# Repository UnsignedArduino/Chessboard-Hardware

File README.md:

[Chessboard-Hardware](https://github.com/UnsignedArduino/Chessboard-Hardware) |
[Chessboard-Design](https://github.com/UnsignedArduino/Chessboard-Design) |
[Chessboard-Nano](https://github.com/UnsignedArduino/Chessboard-Nano) |
[Chessboard-Pi](https://github.com/UnsignedArduino/Chessboard-Pi)

# Chessboard-Hardware

Hardware for a magnetic-piece-tracking digital chessboard! WIP

This repository contains the KiCad PCB project for the majority of the Chessboard's wiring.

## Notes

### Models

All models were modified in Fusion 360. 

* Arduino Nano was modified from [Joel Skerman's model](https://www.thingiverse.com/thing:3863918) and colors are inspired by
  [Raafat Mohamed's model](https://grabcad.com/library/arduino-nano-26).
* SS49E was modified from the [SnapMagic library](https://www.snapeda.com/parts/SS49E/Honeywell/view-part/?ref=digikey).

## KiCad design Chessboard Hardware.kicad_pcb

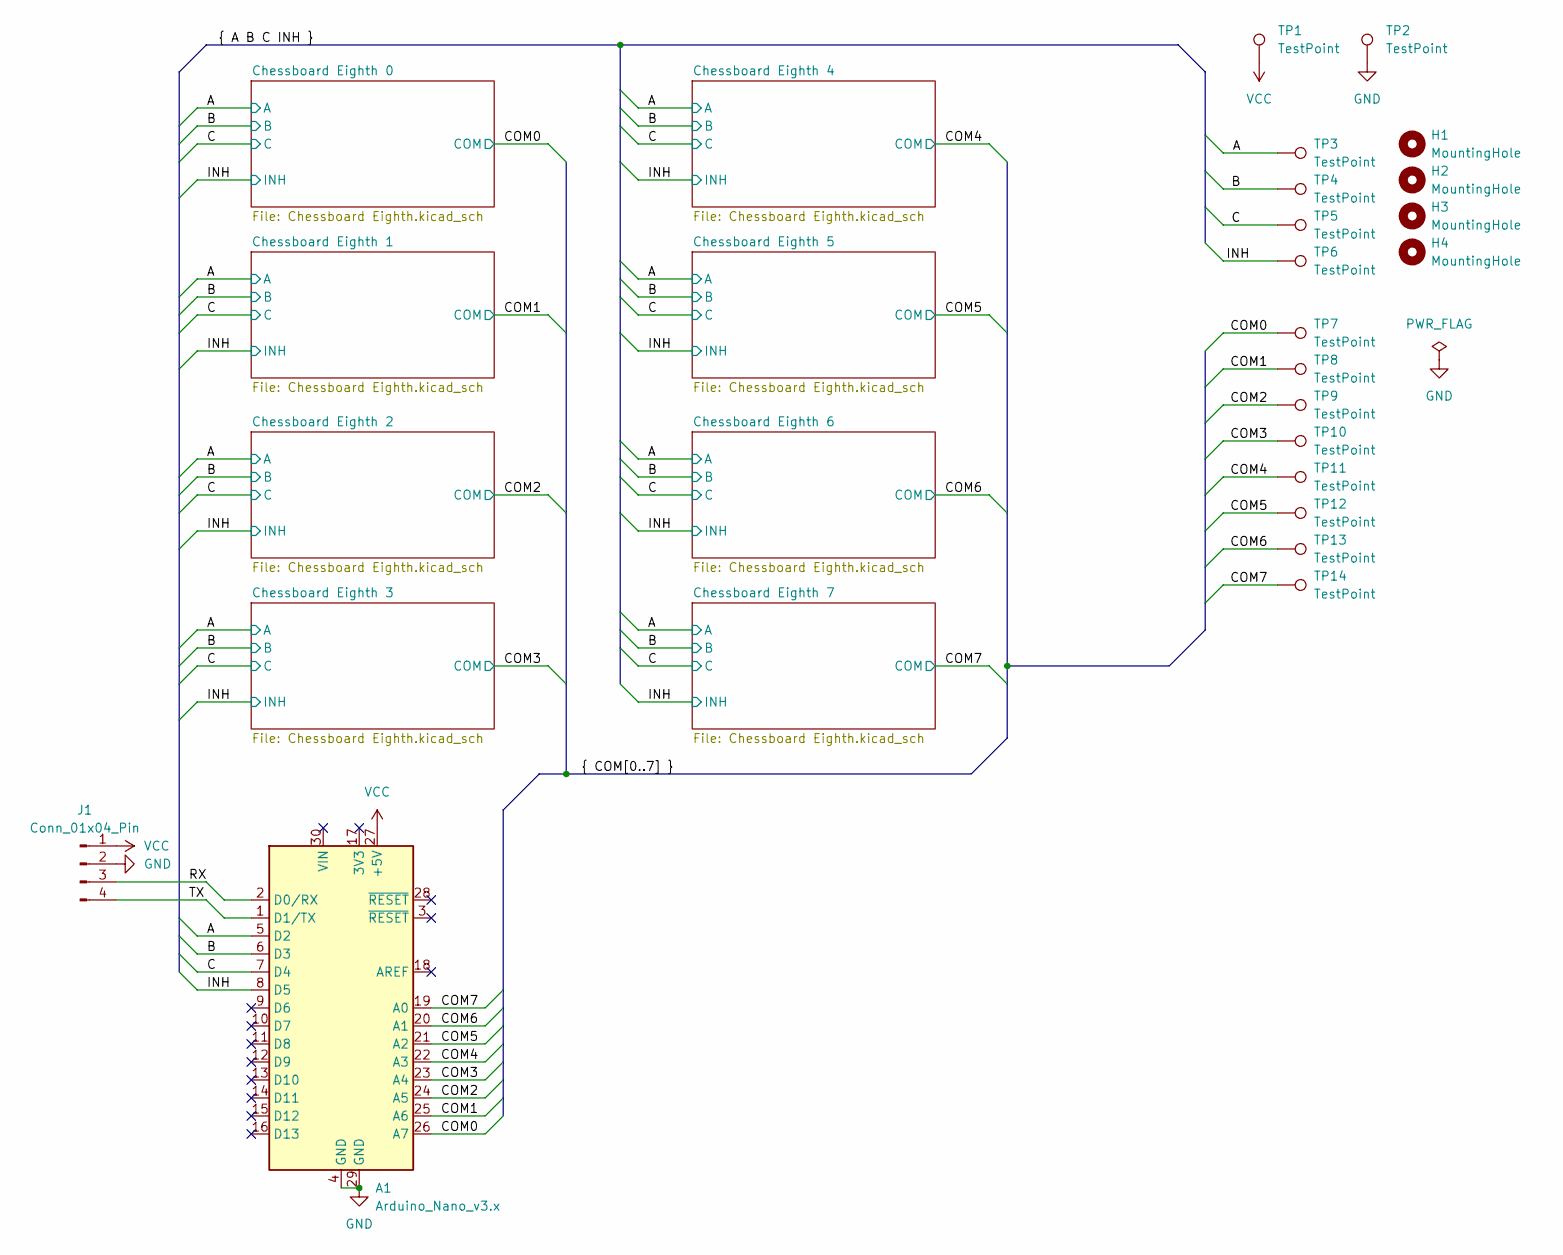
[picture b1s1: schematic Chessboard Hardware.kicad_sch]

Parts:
A1: Arduino_Nano_v3.x; Arduino_Nano
H1, H2, H3, H4: MountingHole; MountingHole_2.7mm_M2.5
J1: Conn_01x04_Pin; JST_XH_B4B-XH-A_1x04_P2.50mm_Vertical
TP1, TP2, TP3, TP4, TP5, TP6, TP7, TP8, TP9, TP10, TP11, TP12, TP13, TP14: TestPoint; PinHeader_1x01_P2.54mm_Vertical

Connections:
/A: A1.5 (D2), TP3.1; also elsewhere on the board
/B: A1.6 (D3), TP4.1; also elsewhere on the board
/C: A1.7 (D4), TP5.1; also elsewhere on the board
/COM0: A1.26 (A7), TP7.1; also elsewhere on the board
/COM1: A1.25 (A6), TP8.1; also elsewhere on the board
/COM2: A1.24 (A5), TP9.1; also elsewhere on the board
/COM3: A1.23 (A4), TP10.1; also elsewhere on the board
/COM4: A1.22 (A3), TP11.1; also elsewhere on the board
/COM5: A1.21 (A2), TP12.1; also elsewhere on the board
/COM6: A1.20 (A1), TP13.1; also elsewhere on the board
/COM7: A1.19 (A0), TP14.1; also elsewhere on the board
/INH: A1.8 (D5), TP6.1; also elsewhere on the board
/RX: A1.2 (D0/RX), J1.3
/TX: A1.1 (D1/TX), J1.4
GND: A1.4 (GND), A1.29 (GND), J1.2, TP2.1; also elsewhere on the board
VCC: A1.27 (+5V), J1.1, TP1.1; also elsewhere on the board

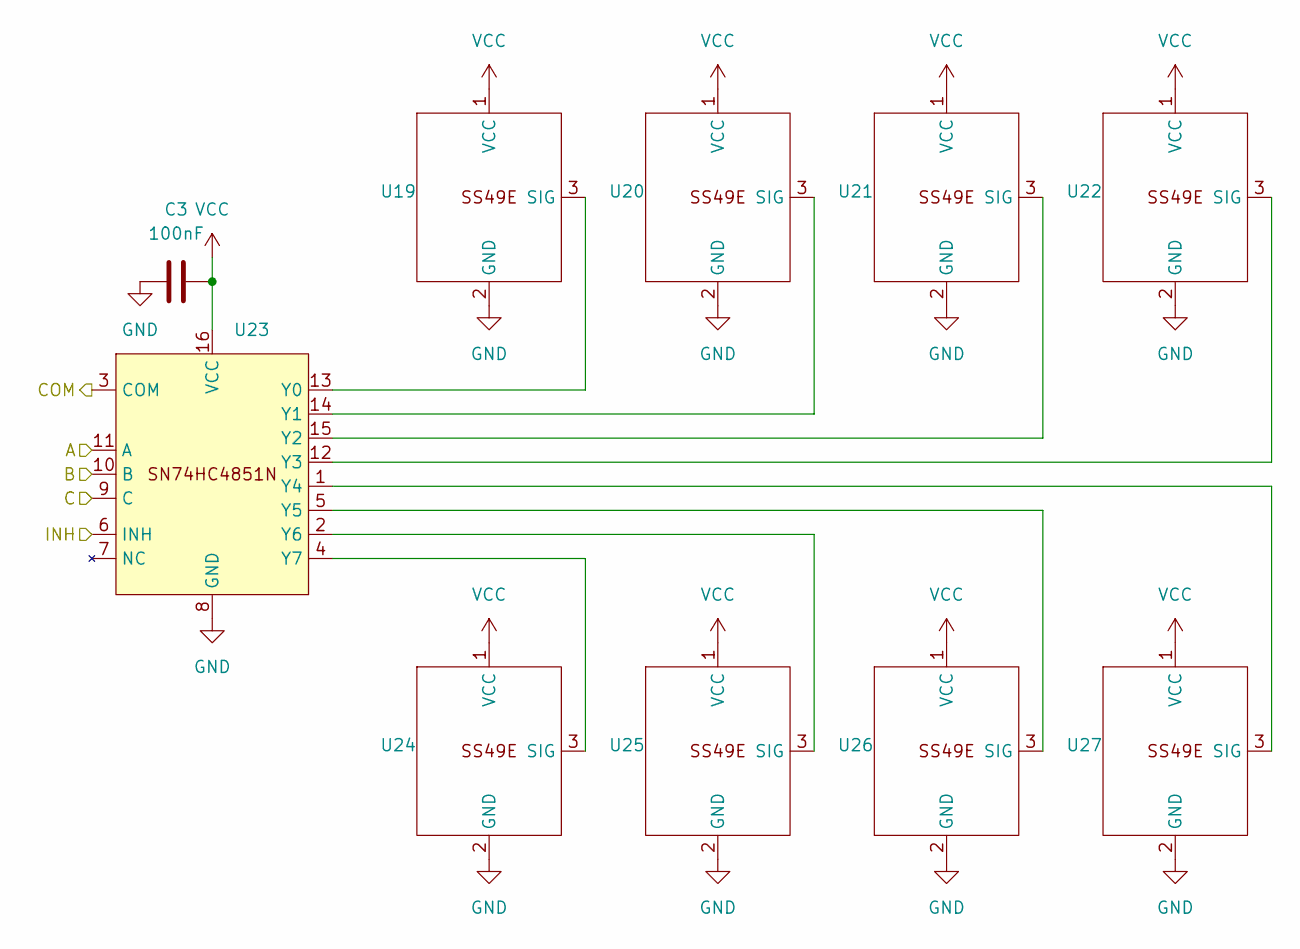
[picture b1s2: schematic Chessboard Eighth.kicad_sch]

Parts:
C3: 100nF; C_Disc_D5.0mm_W2.5mm_P2.50mm
U19, U20, U21, U22, U24, U25, U26, U27: SS49E
U23: DIP-16_W7.62mm

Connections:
/A: U23.11 (A); also elsewhere on the board
/B: U23.10 (B); also elsewhere on the board
/C: U23.9 (C); also elsewhere on the board
/COM2: U23.3 (COM); also elsewhere on the board
/INH: U23.6 (INH); also elsewhere on the board
GND: C3.1, U19.2 (GND), U20.2 (GND), U21.2 (GND), U22.2 (GND), U23.8 (GND), U24.2 (GND), U25.2 (GND), U26.2 (GND), U27.2 (GND); also elsewhere on the board
unnamed: U19.3 (SIG), U23.13 (Y0)
unnamed: U20.3 (SIG), U23.14 (Y1)
unnamed: U21.3 (SIG), U23.15 (Y2)
unnamed: U22.3 (SIG), U23.12 (Y3)
unnamed: U23.1 (Y4), U27.3 (SIG)
unnamed: U23.5 (Y5), U26.3 (SIG)
unnamed: U23.2 (Y6), U25.3 (SIG)
unnamed: U23.4 (Y7), U24.3 (SIG)
VCC: C3.2, U19.1 (VCC), U20.1 (VCC), U21.1 (VCC), U22.1 (VCC), U23.16 (VCC), U24.1 (VCC), U25.1 (VCC), U26.1 (VCC), U27.1 (VCC); also elsewhere on the board

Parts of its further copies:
C1, C2, C4, C5, C6, C7, C8: 100nF; C_Disc_D5.0mm_W2.5mm_P2.50mm
U1, U2, U3, U4, U6, U7, U8, U9, U10, U11, U12, U13, U15, U16, U17, U18, U28, U29, U30, U31, U33, U34, U35, U36, U37, U38, U39, U40, U42, U43, U44, U45, U46, U47, U48, U49, U51, U52, U53, U54, U55, U56, U57, U58, U60, U61, U62, U63, U64, U65, U66, U67, U69, U70, U71, U72: SS49E
U5, U14, U32, U41, U50, U59, U68: DIP-16_W7.62mm

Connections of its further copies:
/A: U5.11 (A), U14.11 (A), U32.11 (A), U41.11 (A), U50.11 (A), U59.11 (A), U68.11 (A); also elsewhere on the board
/B: U5.10 (B), U14.10 (B), U32.10 (B), U41.10 (B), U50.10 (B), U59.10 (B), U68.10 (B); also elsewhere on the board
/C: U5.9 (C), U14.9 (C), U32.9 (C), U41.9 (C), U50.9 (C), U59.9 (C), U68.9 (C); also elsewhere on the board
/COM0: U5.3 (COM); also elsewhere on the board
/COM1: U14.3 (COM); also elsewhere on the board
/COM3: U32.3 (COM); also elsewhere on the board
/COM4: U41.3 (COM); also elsewhere on the board
/COM5: U50.3 (COM); also elsewhere on the board
/COM6: U59.3 (COM); also elsewhere on the board
/COM7: U68.3 (COM); also elsewhere on the board
/INH: U5.6 (INH), U14.6 (INH), U32.6 (INH), U41.6 (INH), U50.6 (INH), U59.6 (INH), U68.6 (INH); also elsewhere on the board
GND: C1.1, C2.1, C4.1, C5.1, C6.1, C7.1, C8.1, U1.2 (GND), U2.2 (GND), U3.2 (GND), U4.2 (GND), U5.8 (GND), U6.2 (GND), U7.2 (GND), U8.2 (GND), U9.2 (GND), U10.2 (GND), U11.2 (GND), U12.2 (GND), U13.2 (GND), U14.8 (GND), U15.2 (GND), U16.2 (GND), U17.2 (GND), U18.2 (GND), U28.2 (GND), U29.2 (GND), U30.2 (GND), U31.2 (GND), U32.8 (GND), U33.2 (GND), U34.2 (GND), U35.2 (GND), U36.2 (GND), U37.2 (GND), U38.2 (GND), U39.2 (GND), U40.2 (GND), U41.8 (GND), U42.2 (GND), U43.2 (GND), U44.2 (GND), U45.2 (GND), U46.2 (GND), U47.2 (GND), U48.2 (GND), U49.2 (GND), U50.8 (GND), U51.2 (GND), U52.2 (GND), U53.2 (GND), U54.2 (GND), U55.2 (GND), U56.2 (GND), U57.2 (GND), U58.2 (GND), U59.8 (GND), U60.2 (GND), U61.2 (GND), U62.2 (GND), U63.2 (GND), U64.2 (GND), U65.2 (GND), U66.2 (GND), U67.2 (GND), U68.8 (GND), U69.2 (GND), U70.2 (GND), U71.2 (GND), U72.2 (GND); also elsewhere on the board
unnamed: U1.3 (SIG), U5.13 (Y0)
unnamed: U2.3 (SIG), U5.14 (Y1)
unnamed: U3.3 (SIG), U5.15 (Y2)
unnamed: U4.3 (SIG), U5.12 (Y3)
unnamed: U5.1 (Y4), U9.3 (SIG)
unnamed: U5.5 (Y5), U8.3 (SIG)
unnamed: U5.2 (Y6), U7.3 (SIG)
unnamed: U5.4 (Y7), U6.3 (SIG)
unnamed: U10.3 (SIG), U14.13 (Y0)
unnamed: U11.3 (SIG), U14.14 (Y1)
unnamed: U12.3 (SIG), U14.15 (Y2)
unnamed: U13.3 (SIG), U14.12 (Y3)
unnamed: U14.1 (Y4), U18.3 (SIG)
unnamed: U14.5 (Y5), U17.3 (SIG)
unnamed: U14.2 (Y6), U16.3 (SIG)
unnamed: U14.4 (Y7), U15.3 (SIG)
unnamed: U28.3 (SIG), U32.13 (Y0)
unnamed: U29.3 (SIG), U32.14 (Y1)
unnamed: U30.3 (SIG), U32.15 (Y2)
unnamed: U31.3 (SIG), U32.12 (Y3)
unnamed: U32.1 (Y4), U36.3 (SIG)
unnamed: U32.5 (Y5), U35.3 (SIG)
unnamed: U32.2 (Y6), U34.3 (SIG)
unnamed: U32.4 (Y7), U33.3 (SIG)
unnamed: U37.3 (SIG), U41.13 (Y0)
unnamed: U38.3 (SIG), U41.14 (Y1)
unnamed: U39.3 (SIG), U41.15 (Y2)
unnamed: U40.3 (SIG), U41.12 (Y3)
unnamed: U41.1 (Y4), U45.3 (SIG)
unnamed: U41.5 (Y5), U44.3 (SIG)
unnamed: U41.2 (Y6), U43.3 (SIG)
unnamed: U41.4 (Y7), U42.3 (SIG)
unnamed: U46.3 (SIG), U50.13 (Y0)
unnamed: U47.3 (SIG), U50.14 (Y1)
unnamed: U48.3 (SIG), U50.15 (Y2)
unnamed: U49.3 (SIG), U50.12 (Y3)
unnamed: U50.1 (Y4), U54.3 (SIG)
unnamed: U50.5 (Y5), U53.3 (SIG)
unnamed: U50.2 (Y6), U52.3 (SIG)
unnamed: U50.4 (Y7), U51.3 (SIG)
unnamed: U55.3 (SIG), U59.13 (Y0)
unnamed: U56.3 (SIG), U59.14 (Y1)
unnamed: U57.3 (SIG), U59.15 (Y2)
unnamed: U58.3 (SIG), U59.12 (Y3)
unnamed: U59.1 (Y4), U63.3 (SIG)
unnamed: U59.5 (Y5), U62.3 (SIG)
unnamed: U59.2 (Y6), U61.3 (SIG)
unnamed: U59.4 (Y7), U60.3 (SIG)
unnamed: U64.3 (SIG), U68.13 (Y0)
unnamed: U65.3 (SIG), U68.14 (Y1)
unnamed: U66.3 (SIG), U68.15 (Y2)
unnamed: U67.3 (SIG), U68.12 (Y3)
unnamed: U68.1 (Y4), U72.3 (SIG)
unnamed: U68.5 (Y5), U71.3 (SIG)
unnamed: U68.2 (Y6), U70.3 (SIG)
unnamed: U68.4 (Y7), U69.3 (SIG)
VCC: C1.2, C2.2, C4.2, C5.2, C6.2, C7.2, C8.2, U1.1 (VCC), U2.1 (VCC), U3.1 (VCC), U4.1 (VCC), U5.16 (VCC), U6.1 (VCC), U7.1 (VCC), U8.1 (VCC), U9.1 (VCC), U10.1 (VCC), U11.1 (VCC), U12.1 (VCC), U13.1 (VCC), U14.16 (VCC), U15.1 (VCC), U16.1 (VCC), U17.1 (VCC), U18.1 (VCC), U28.1 (VCC), U29.1 (VCC), U30.1 (VCC), U31.1 (VCC), U32.16 (VCC), U33.1 (VCC), U34.1 (VCC), U35.1 (VCC), U36.1 (VCC), U37.1 (VCC), U38.1 (VCC), U39.1 (VCC), U40.1 (VCC), U41.16 (VCC), U42.1 (VCC), U43.1 (VCC), U44.1 (VCC), U45.1 (VCC), U46.1 (VCC), U47.1 (VCC), U48.1 (VCC), U49.1 (VCC), U50.16 (VCC), U51.1 (VCC), U52.1 (VCC), U53.1 (VCC), U54.1 (VCC), U55.1 (VCC), U56.1 (VCC), U57.1 (VCC), U58.1 (VCC), U59.16 (VCC), U60.1 (VCC), U61.1 (VCC), U62.1 (VCC), U63.1 (VCC), U64.1 (VCC), U65.1 (VCC), U66.1 (VCC), U67.1 (VCC), U68.16 (VCC), U69.1 (VCC), U70.1 (VCC), U71.1 (VCC), U72.1 (VCC); also elsewhere on the board

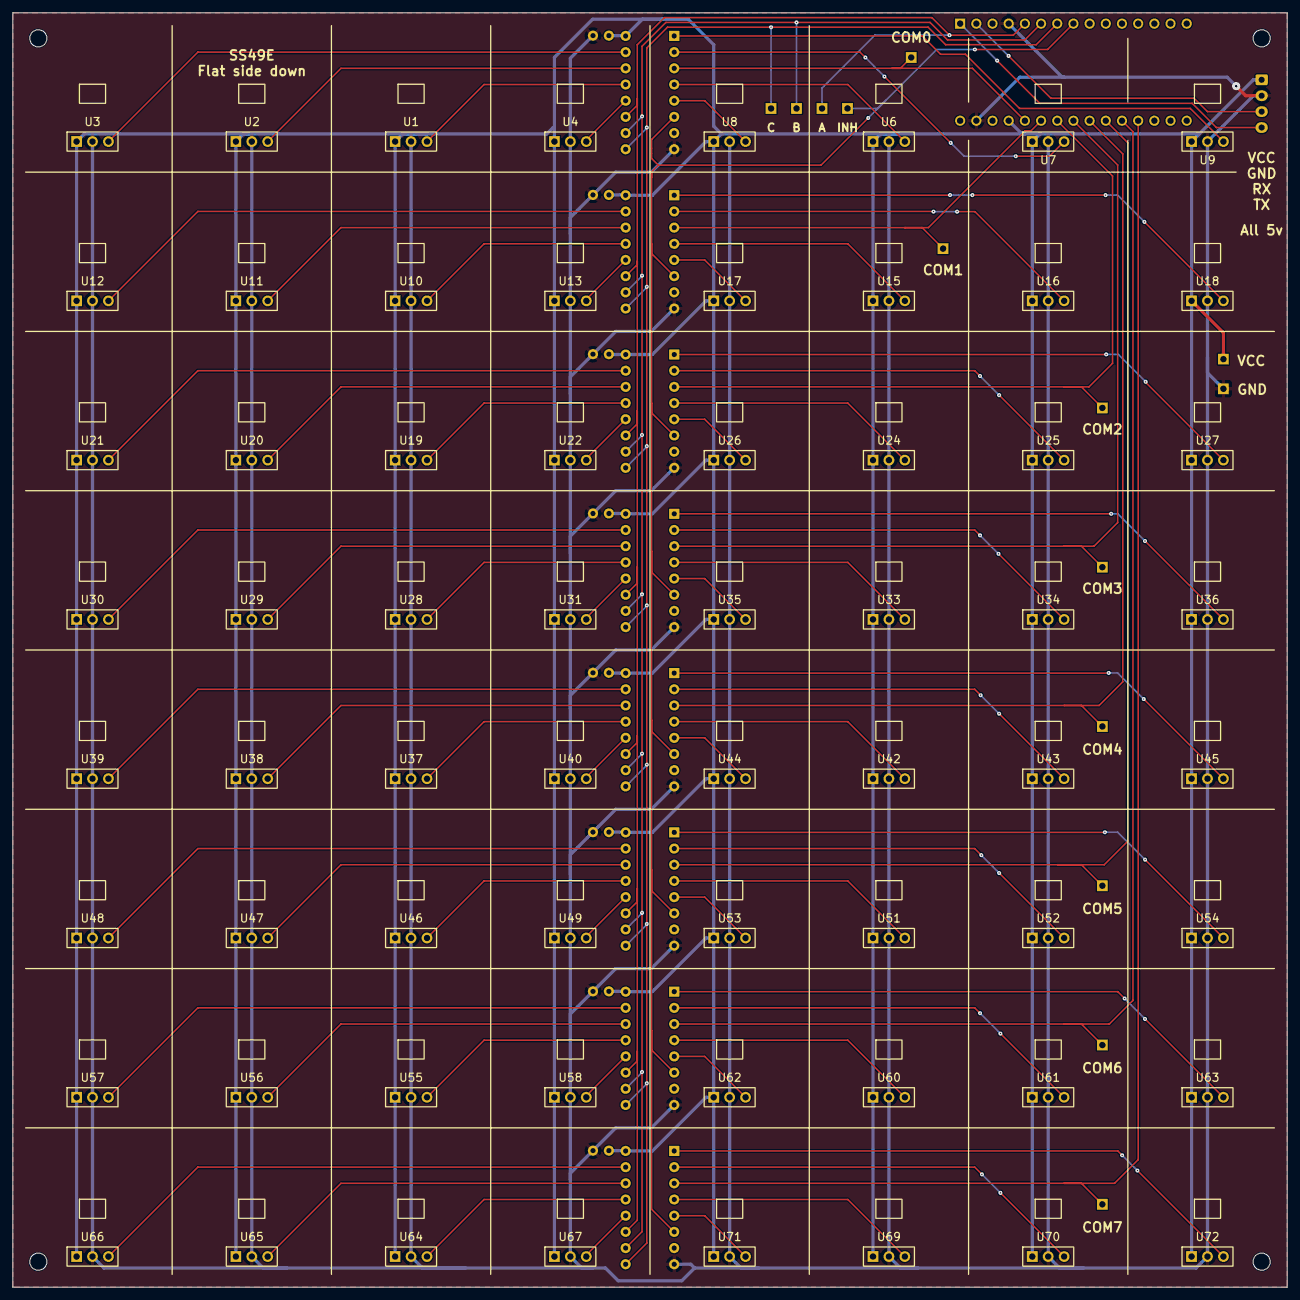
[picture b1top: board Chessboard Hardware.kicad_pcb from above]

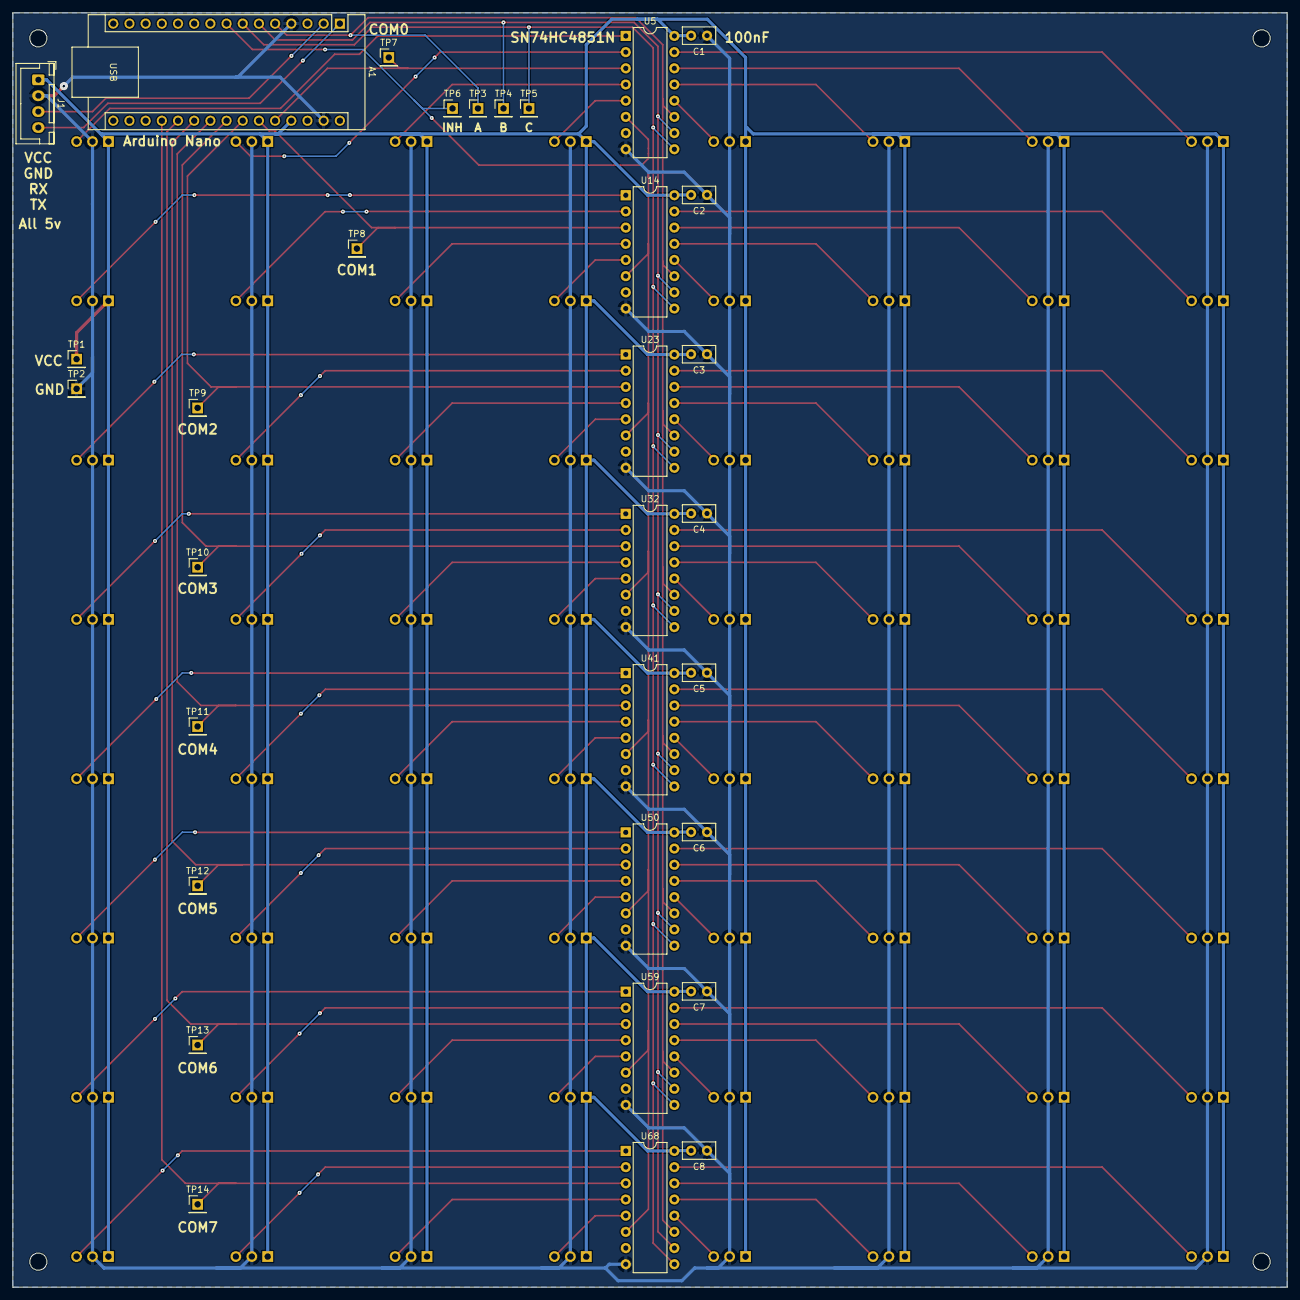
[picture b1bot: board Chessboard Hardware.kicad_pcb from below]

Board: 2 copper layers, 200.0 x 200.0 mm, 100 parts (32 on the bottom side), 80 nets.

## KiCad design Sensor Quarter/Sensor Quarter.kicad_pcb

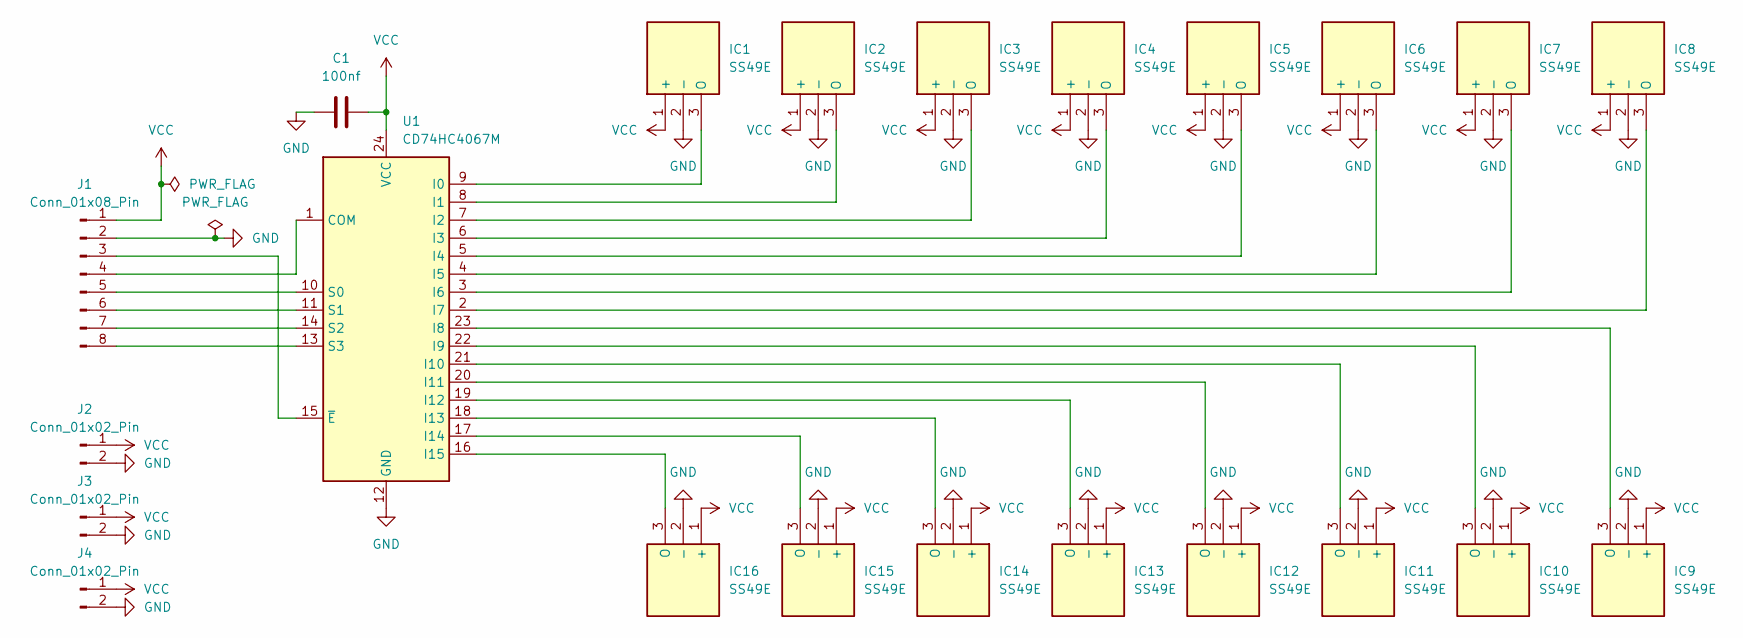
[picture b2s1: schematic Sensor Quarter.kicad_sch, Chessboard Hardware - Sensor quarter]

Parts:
C1: 100nf; C_Disc_D5.0mm_W2.5mm_P2.50mm
IC1, IC2, IC3, IC4, IC5, IC6, IC7, IC8, IC9, IC10, IC11, IC12, IC13, IC14, IC15, IC16: SS49E; TO130P160X410X300-3P; Manufacturer_Part_Number SS49E; Mouser Part Number 785-SS49E
J1: Conn_01x08_Pin; PinHeader_1x08_P2.54mm_Vertical
J2, J3, J4: Conn_01x02_Pin; PinHeader_1x02_P2.54mm_Vertical
U1: CD74HC4067M; SOIC-24W_7.5x15.4mm_P1.27mm

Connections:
GND: C1.1, IC1.2 (-), IC2.2 (-), IC3.2 (-), IC4.2 (-), IC5.2 (-), IC6.2 (-), IC7.2 (-), IC8.2 (-), IC9.2 (-), IC10.2 (-), IC11.2 (-), IC12.2 (-), IC13.2 (-), IC14.2 (-), IC15.2 (-), IC16.2 (-), J1.2, J2.2, J3.2, J4.2, U1.12 (GND)
unnamed: IC1.3 (O), U1.9 (I0)
unnamed: IC2.3 (O), U1.8 (I1)
unnamed: IC3.3 (O), U1.7 (I2)
unnamed: IC4.3 (O), U1.6 (I3)
unnamed: IC5.3 (O), U1.5 (I4)
unnamed: IC6.3 (O), U1.4 (I5)
unnamed: IC7.3 (O), U1.3 (I6)
unnamed: IC8.3 (O), U1.2 (I7)
unnamed: IC9.3 (O), U1.23 (I8)
unnamed: IC10.3 (O), U1.22 (I9)
unnamed: IC11.3 (O), U1.21 (I10)
unnamed: IC12.3 (O), U1.20 (I11)
unnamed: IC13.3 (O), U1.19 (I12)
unnamed: IC14.3 (O), U1.18 (I13)
unnamed: IC15.3 (O), U1.17 (I14)
unnamed: IC16.3 (O), U1.16 (I15)
unnamed: J1.3, U1.15 (~E)
unnamed: J1.4, U1.1 (COM)
unnamed: J1.5, U1.10 (S0)
unnamed: J1.6, U1.11 (S1)
unnamed: J1.7, U1.14 (S2)
unnamed: J1.8, U1.13 (S3)
VCC: C1.2, IC1.1 (+), IC2.1 (+), IC3.1 (+), IC4.1 (+), IC5.1 (+), IC6.1 (+), IC7.1 (+), IC8.1 (+), IC9.1 (+), IC10.1 (+), IC11.1 (+), IC12.1 (+), IC13.1 (+), IC14.1 (+), IC15.1 (+), IC16.1 (+), J1.1, J2.1, J3.1, J4.1, U1.24 (VCC)

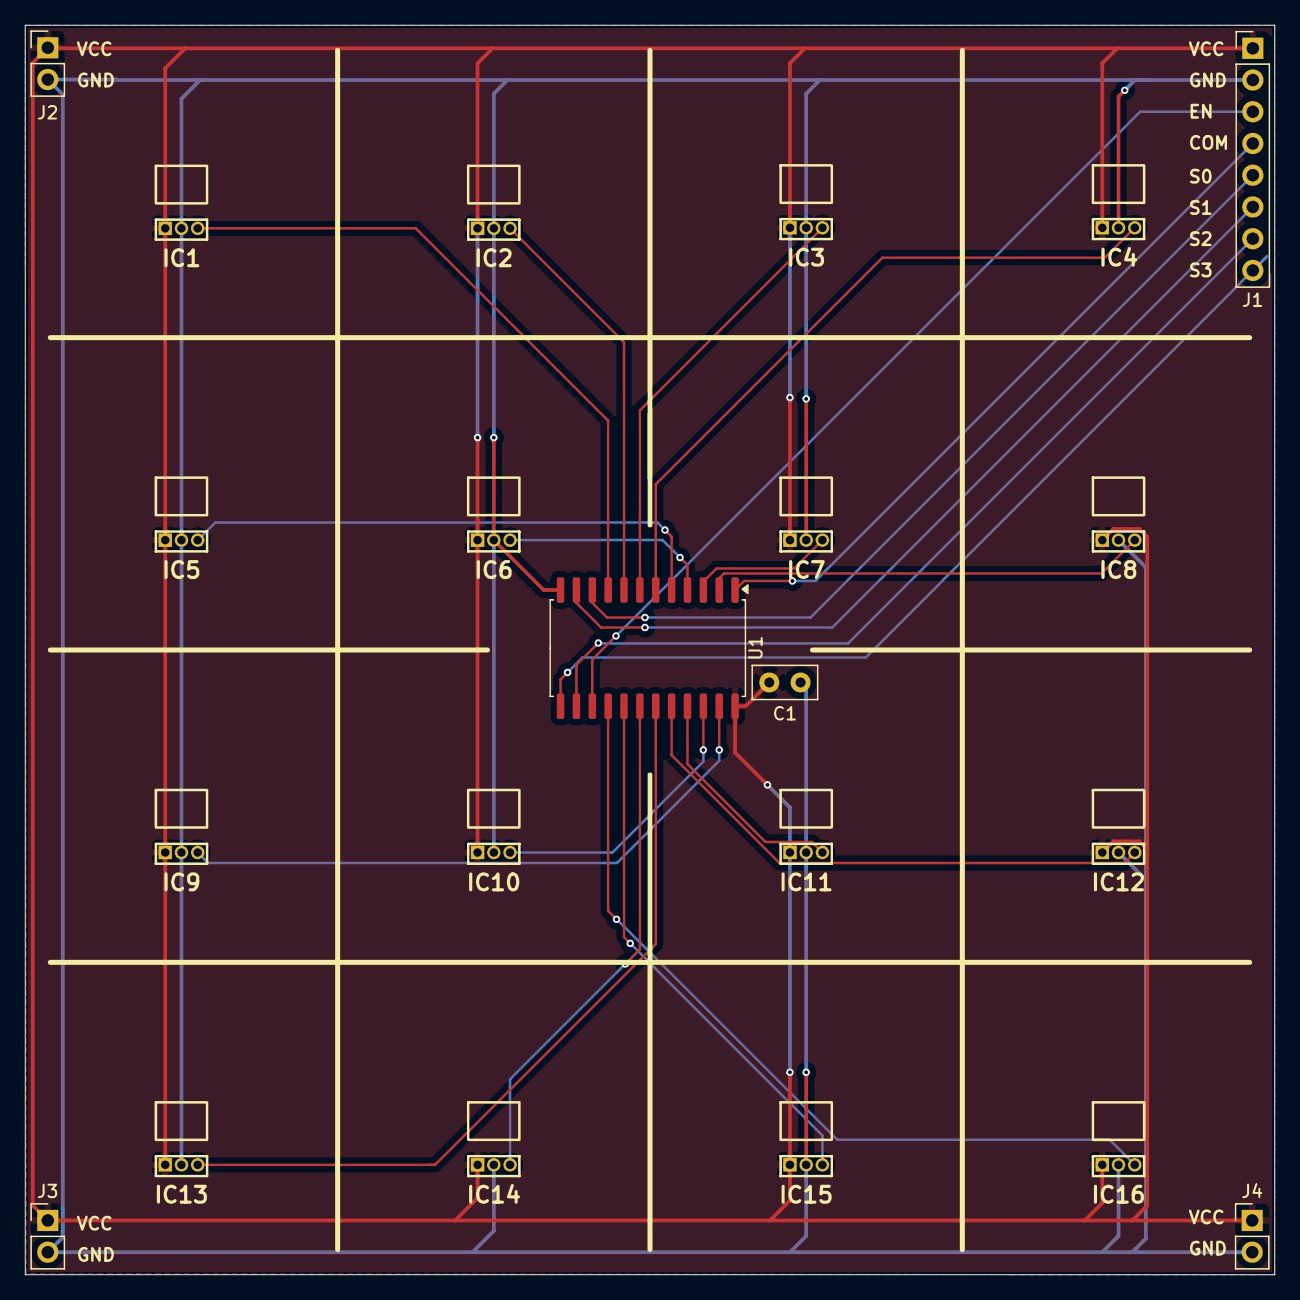
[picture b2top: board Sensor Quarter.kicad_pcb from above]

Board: 2 copper layers, 100.0 x 100.0 mm, 22 parts (0 on the bottom side), 24 nets.

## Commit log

2025-01-24 Empty project
2025-01-24 Schematic for sensor quarter
2025-01-24 Start PCB, add lines for layout
2025-01-24 Layout SSe49s
2025-01-24 PCB done
2025-01-24 VCC plane
2025-01-24 Widen power traces
2025-01-25 I forgot what I did
2025-01-25 Move to own directory because we'll have multiple KiCad projects
2025-01-25 Again
2025-02-01 Redo
2025-02-01 Schematic done
2025-02-01 Start PCB
2025-02-01 Silkscreen lines for center of chess squares on PCB
2025-02-02 Lets try this again
2025-02-02 Line up linear halls
2025-02-02 Everything except linear halls routed
2025-02-02 Autoroute and cleanup linear hall traces
2025-02-02 Done
2025-02-03 Done and Gerbers
2025-02-05 Add 4 pin header to all sides for convenience
2025-02-05 Remove locks
2025-02-05 I2C pull ups
2025-02-05 README update
2025-02-05 Create LICENSE
2025-02-07 Cleanup
2025-02-08 Redo footprint for SS49E, finish linear hall layouts
2025-02-08 Remove silkscreen guides
2025-02-08 Done routing again
2025-02-08 Ok actually done
2025-02-08 Slightly better model
2025-02-08 Bye bye lets try again
2025-02-08 From template
2025-02-08 Finish settings
2025-02-09 Add symbols and footprints
2025-02-09 Schematic
2025-02-09 Reannoate
2025-02-10 Simpler schematic with one less chip, use UART for comms
2025-02-10 Refactor looks
2025-02-11 Alignment lines again for the billionth time
2025-02-11 Start placing first two rows of linear halls and muxes
2025-02-11 Finish linear hall layout again
2025-02-11 Remove silkscreen guidelines
2025-02-11 Layout mounting holes, update SS49E footprint to be smaller
2025-02-11 Oops forgot decoupling caps
2025-02-11 Finish placing except test points, which have 2.54 pin header footprint now
2025-02-11 Start routing
2025-02-12 Done routing everything except linear halls
2025-02-12 Finish routing
    With help from Freerouting
2025-02-12 Cleanup routing
2025-02-12 Fill zones, add helpful skillscreen text
2025-02-15 Fix alignment and sizes
2025-02-16 Move pieces for not overlapping names
2025-02-16 Oh man we're doing this again
2025-02-16 First row done
2025-02-16 Four rows of linear halls done
2025-02-16 Finish linear hall placement
2025-02-16 Finish layout
2025-02-16 Remove silkscreen guidelines (layout actually done now)
2025-02-16 Add Arduino Nano model
2025-02-17 Add SS49E model
2025-02-17 Fix Arduino Nano position
2025-02-17 Route signal lines
2025-02-17 Route left side linear halls
2025-02-17 Finish routing linear halls
2025-02-17 Finish test pad routing
2025-02-17 Ground plane
2025-02-17 Done with silkscreens
2025-02-19 Ground pour on top layer
2025-02-20 Change INH trace a tiny bit for no right angle connection
2025-02-20 JST XH connector
2025-02-20 Oopsie forgot to refill zone
2025-03-10 Update Arduino Nano model so pin header solder joints don't suck
2025-03-10 Update something
2025-04-04 Revert "Update README.md"
    This reverts commit 77b24e4571037374f43b0996b18b1578ad540709.
2025-04-14 Update BOM export settings
